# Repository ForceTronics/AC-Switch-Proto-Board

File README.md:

# AC-Switch-Proto-Board
Eagle PCB layout for a development board that allows you to switch AC line power using a TRIAC. The board is for ~150VACrms and up to 2A. 
The custom parts used in this design can be accessed from the ForceTronics.lbr, to add this file to the Eagle Library put it in the Eagle folder "lbr"
For a detailed description of this board and how to use it check out the YouTube video https://youtu.be/cWqB3ttuddQ
If you would like to purchase this board go to www.forcetronics.com

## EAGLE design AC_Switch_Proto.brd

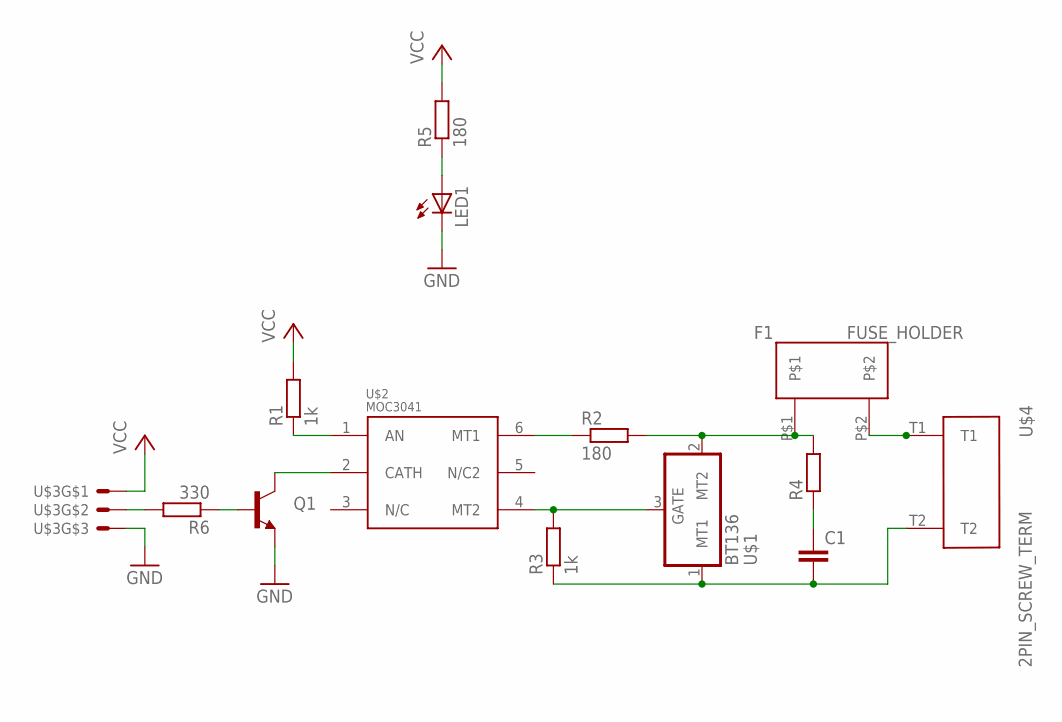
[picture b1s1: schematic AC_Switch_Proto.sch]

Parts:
C1: C-EU050-030X075; C050-030X075
F1: FUSE_HOLDER
LED1: LED3MM
Q1: TRANSISTOR_NPNBC547; TO-92-AMMO
R1, R3: 1k; 0207/10
R2, R5: 180; 0207/10
R4: R0207/10; 0207/10
R6: 330; 0207/10
U$1: BT136
U$2: MOC3041
U$3: 3PINHEADER
U$4: 2PIN_SCREW_TERM

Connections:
GND: LED1.K (C), Q1.3 (E), U$3.N2
unnamed: R6.2, U$3.N1
unnamed: Q1.1 (C), U$2.2 (CATH)
unnamed: R1.1, U$2.1 (AN)
unnamed: Q1.2 (B), R6.1
unnamed: F1.P$1, R2.2, R4.2, U$1.2 (MT2)
unnamed: R2.1, U$2.6 (MT1)
unnamed: C1.2, R3.1, U$1.1 (MT1), U$4.T2
unnamed: R3.2, U$1.3 (GATE), U$2.4 (MT2)
unnamed: F1.P$2, U$4.T1
unnamed: C1.1, R4.1
unnamed: LED1.A, R5.1
VCC: R1.2, R5.2, U$3.N0

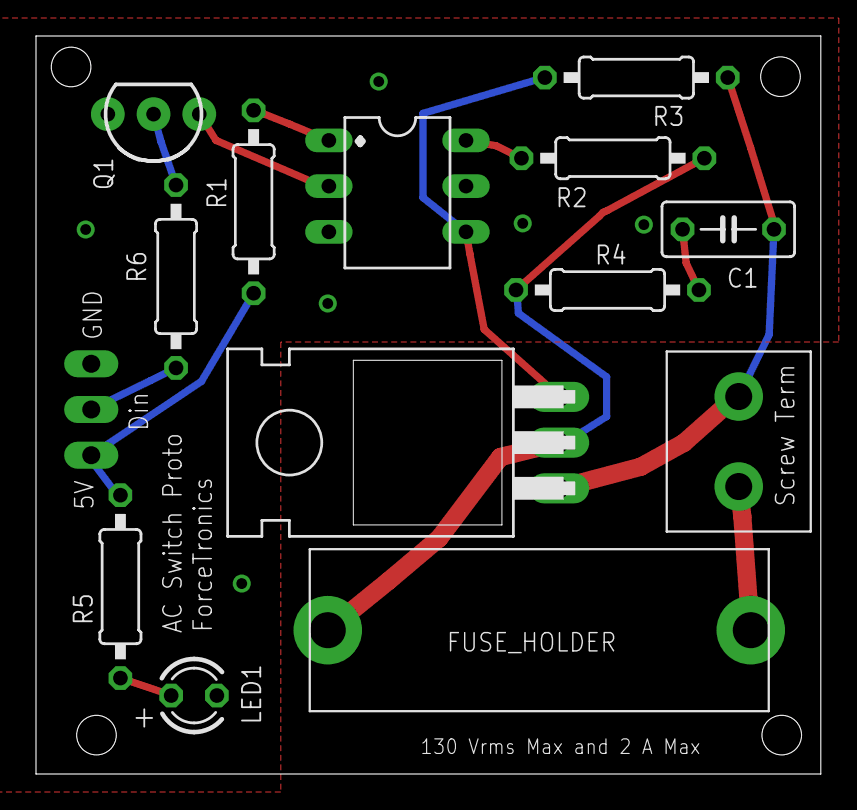
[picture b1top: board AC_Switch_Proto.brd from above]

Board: 2 copper layers, 43.6 x 41.0 mm, 14 parts (0 on the bottom side), 13 nets.

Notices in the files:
parts and their libraries:
SparkFun-DiscreteSemi: Licensing: Creative Commons ShareAlike 4.0 International - https://creativecommons.org/licenses/by-sa/4.0
